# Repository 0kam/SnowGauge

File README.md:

<p align="center">
  <picture>
    <source media="(prefers-color-scheme: dark)" srcset="docs/assets/logo/logo_dark_800.png">
    
  </picture>
</p>

# SnowGauge

山岳・亜高山帯の無人サイトで 2 年間動く、低価格・低消費電力の積雪深ロガーです。
近赤外レーザー測距（TFmini Plus）で雪面までの斜距離を測り、IMU の傾斜で補正して積雪深に換算します。
スマホ（Android Chrome）の Web Bluetooth ページで時刻合わせ・データ回収・設定を行い、電池だけで越冬します。

*SnowGauge is a low-cost, low-power snow-depth logger (NIR laser ToF + XIAO nRF52840 Sense, Zephyr firmware, Web Bluetooth field app). Documentation is in Japanese; the developer docs (`firmware/README.md`, `docs/app/README.md`, `docs/record_format.md`) are in English.*

## はじめての方へ（この順に読む）

| 段階 | 読むもの | 内容 |
|---|---|---|
| 1. 部品を買う | [docs/01_parts.md](docs/01_parts.md)（[CSV](docs/01_parts.csv)） | 購入リスト。基板版・ブレッドボード版・TSD20 版の差分 |
| 2. 組み立てる | [docs/02_assembly.md](docs/02_assembly.md) | ブレッドボード（[配線ガイド](https://0kam.github.io/SnowGauge/breadboard_guide.html)）／基板 v1.2／筐体（検討中） |
| 3. ファームを書く | [docs/03_firmware.md](docs/03_firmware.md) | [Release](https://github.com/0kam/SnowGauge/releases) からダウンロードして USB で書き込み |
| 4. アプリを入れる・使う | [docs/04_app.md](docs/04_app.md) | **アプリ: https://0kam.github.io/SnowGauge/app/** 設置時・巡回時の手順 |
| 5. データを見る | [docs/05_data.md](docs/05_data.md) | CSV の列、品質フラグ、積雪深の再計算 |

文書一覧と「どこを直すとき何を更新するか」は [docs/README.md](docs/README.md) にあります。

## 現地アプリ

スマホの Chrome で https://0kam.github.io/SnowGauge/app/ を開き「ホーム画面に追加」すると、圏外でも起動するアプリになります（[使い方](docs/04_app.md)）。本体なしで画面を試すには [デモ表示](https://0kam.github.io/SnowGauge/app/?demo=1)。

<table align="center"><tr>
  <td valign="top" width="25%"></td>
  <td valign="top" width="25%"></td>
  <td valign="top" width="25%"></td>
  <td valign="top" width="25%"></td>
</tr><tr>
  <td align="center">1. 同期</td><td align="center">2. 観測データ</td><td align="center">3. スケジュール</td><td align="center">4. 設置・基準設定</td>
</tr></table>

## 主な仕様

- 測距: TFmini Plus（近赤外 ToF）。安価な代替として TSD20 版を A/B 比較予定
- MCU: Seeed XIAO nRF52840 Sense（BLE、IMU 内蔵）、Zephyr（nRF Connect SDK v3.4.0）
- 電源: リチウム単 3（Energizer L91）×4。実測スリープ 26 µA（BLE アドバタイズ込み）、測定 1 回 0.037 mAh
- 記録: 40 バイト/回、QSPI フラッシュ上の LittleFS ＋ 内蔵フラッシュへのミラー。8 回/日で 2 年以上
- 通信: BLE（アドバタイズに電池・件数・最終値、SMP でファイル取得と時刻同期、キャリブレーション用 GATT）
- 現地 UI: Web Bluetooth ページ（PWA、オフライン動作、手袋前提の大きなボタン）

## 開発者向け

- 設計仕様書（要件・設計判断・改版履歴）: [SnowGauge_設計仕様書_v0.16.md](SnowGauge_設計仕様書_v0.16.md)
- 基板（KiCad、ガーバー、ピンマップの正）: [pcb/README.md](pcb/README.md)
- ファームウェアのビルド・シェル: [firmware/README.md](firmware/README.md)
- アプリの構成（SMP クライアントの流用方法）: [docs/app/README.md](docs/app/README.md)
- レコード形式・CSV 列定義: [docs/record_format.md](docs/record_format.md)
- 作業引き継ぎ（AI エージェント向け）: [CLAUDE.md](CLAUDE.md)

## 状態（2026-09-04）

基板 v1.2 発注済み（到着 9/10 ごろ）。ブレッドボードでファームウェア（ステップ 1〜4）とアプリの実機確認まで完了。TSD20 版ファームウェア（ステップ 5）は実装・ビルド済みで、ブレッドボード（U2 を F33 に差し替え）での実機確認待ち。次は基板到着後の再測定、筐体。

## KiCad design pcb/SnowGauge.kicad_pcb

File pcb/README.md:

# SnowGauge PCB v1.2 (TFmini Plus / TSD20 common board)

- Board: **64 x 50 mm**, 2-layer, all through-hole. Bottom layer is a GND pour.
- Mounting: 4x M3 (3.2mm) holes at the corners, **57 x 43 mm** center spacing (3.5mm from every edge; hole centers at (3.5, 3.5) / (60.5, 3.5) / (3.5, 46.5) / (60.5, 46.5) from the board's top-left corner).
- Fits the previous prototype enclosure (Takachi BCAP091208G, inner 66 x 96 mm) with the 50mm side across the width.
- Battery terminal J1 exits at the bottom edge; TFmini terminal J2 exits at the right edge.
- Generated programmatically: [generate_board.py](generate_board.py) → `SnowGauge.kicad_pcb` (KiCad 10). DRC: 0 errors, 0 unconnected.
- One board serves both variants: **U2 = NJU7223F50 for TFmini Plus / NJU7223F33 for TSD20** (same pinout).

## Ordering (JLCPCB, ~1 week to Japan)

1. Go to jlcpcb.com → "Add gerber file" → upload `SnowGauge_v1.2_gerbers.zip`
2. Settings: 2 layers, 64x50mm (auto-detected), qty 5 (or 10), 1.6mm, HASL, green — all defaults are fine
3. Shipping: **DHL or OCS Express** (this is what makes it arrive in ~3-4 days; economy mail takes weeks)

## Firmware pin map (matches this board — the single source of truth)

| XIAO pin | Net | Function |
|---|---|---|
| A0 (D0) | ADC_NODE | Battery voltage = reading x2. Divider hangs on VBAT_SW, so **enable SENSOR_EN, then read A0** (v1.2: Q3/R6/D3 deleted — node is 0V during sleep, never above VDD) |
| D4 / D5 | I2C_SDA / I2C_SCL | Spare I2C header J3 (future external IMU) |
| D6 (TX) | UART_TX_MCU | → 1k (R7) → TFmini RX (white) |
| D7 (RX) | UART_RX | ← TFmini TX (green) |
| **D10** | SENSOR_EN | High = sensor rail ON (Q2→Q1). *Changed from D2 in the hand-wiring plan.* |
| 3V3 | 3V3_SYS | Powered from U1 (NJU7223F33) |

## Connectors

- J1 (screw terminal 2P, 5.08mm): battery + / − ("+"/"-" on silk)
- J2 (4 positions at 5.08mm = **two interlocked 2P blocks**): TFmini, top to bottom RED +5V / BLK GND / GRN TX / WHT RX
- J3 (pin header 1x4): SCL / SDA / GND / 3V3 spare I2C
- A1: 2x low-profile 1x7 female headers (2.54mm) — socket for XIAO nRF52840 Sense

## Extra BOM lines (in addition to spec §6)

| Part | Qty | Note |
|---|---|---|
| Screw terminal block 2P, **5.08mm pitch, interlocking** (TB111-2 / MKDS-1,5 type) | 3 | J1 battery; J2 = 2 blocks snapped together (4 contiguous positions) |
| Female pin socket 1x7, 2.54mm | 2 | XIAO socket. Holes are 0.89mm: fine for round machined tails (~0.5mm) and typical stamped tails; avoid 0.64mm square-tail types |
| 10uF radial MLCC, **5mm lead pitch** | 1 | C6. A 2.5mm-pitch part needs its leads splayed |
| Pin header 1x4, 2.54mm | 1 | J3 (optional) |
| M3 screws/standoffs | 4 | mounting holes at corners |

The consolidated BOM for a whole unit (spec §6 parts + these lines, corrected counts, breadboard consumables, TSD20 variant) is [docs/01_parts.md](../docs/01_parts.md) / [docs/01_parts.csv](../docs/01_parts.csv).

## Safety notes silkscreened on the board

- "NO USB WHILE BATTERY CONNECTED!" — disconnect battery before plugging USB into the XIAO
- C4 (OS-CON) polarity marked; D1 cathode marked "K"

## Component orientation (U1, U2, Q1, Q2)

The KiCad TO-220 / TO-251 vertical footprints put the reference designator on the **metal-tab side**, so the part's **marked (printed) face points the other way**. With the board held "SnowGauge v1.2" up / J1 down: U1 and Q1 have the tab towards the top edge (print facing the XIAO), U2 and Q2 are rotated 180 deg (tab towards the board centre, print facing the top edge). Assembly instructions with a figure: [docs/02_assembly.md](../docs/02_assembly.md) B-2 (figure regenerated by `docs/assets/figures/gen_component_orientation.py`).

## v1.2 changes (post-review)

- **Battery divider now fed from VBAT_SW** (the switched rail) instead of VBAT: the ADC node sits at 0V during sleep instead of floating to ~7V through the nRF52840's clamp diode (abs-max violation found in review). Q3, R6 and the D3 GPIO are deleted. Firmware measures battery by enabling SENSOR_EN and reading A0 (x2).
- **USB corridor cleared**: U1 and C1 moved to the top-left, D1 lowered — a USB-C cable now reaches the socketed XIAO for flashing.
- TFmini wire-order legend moved where it stays visible after C4 is mounted.
- Terminals changed to **3x 5.08mm 2P blocks**; the TFmini pair interlocks into one 4P unit on contiguous 5.08mm positions (J2). Standard Akizuki TB111-class parts drop in.

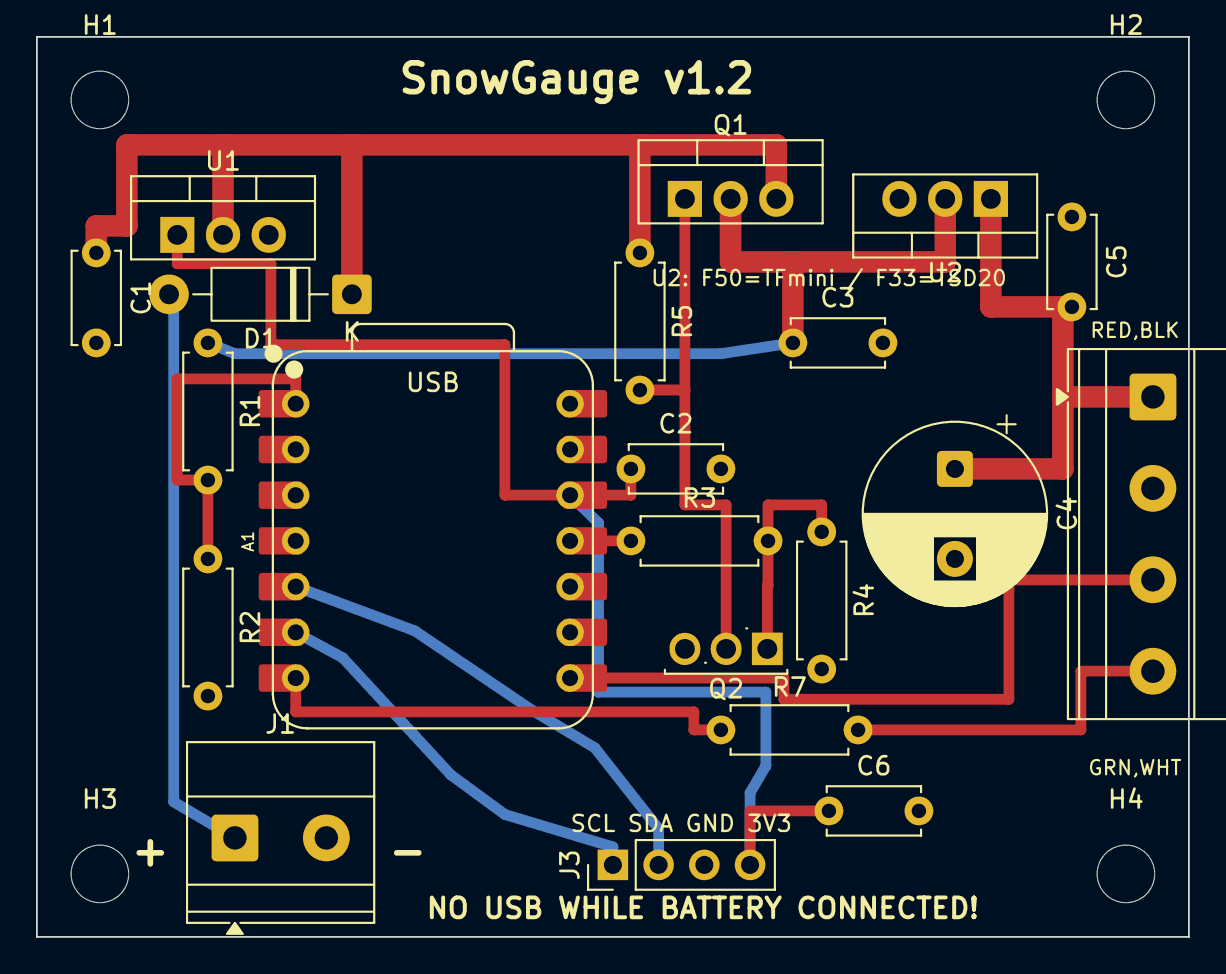
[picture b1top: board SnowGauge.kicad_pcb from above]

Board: 2 copper layers, 64.0 x 50.0 mm, 25 parts (0 on the bottom side), 15 nets.

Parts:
A1: XIAO nRF52840 Sense; XIAO-nRF52840-DIP
C1, C2, C3, C5: 0.1u; C_Disc_D5.0mm_W2.5mm_P5.00mm
C4: OS-CON 470u/16V; CP_Radial_D10.0mm_P5.00mm
C6: 10u; C_Disc_D5.0mm_W2.5mm_P5.00mm
D1: 1N5819; D_DO-41_SOD81_P10.16mm_Horizontal
H1, H2, H3, H4: M3; MountingHole_3.2mm_M3
J1: BATTERY L91x4; TerminalBlock_Phoenix_MKDS-1,5-2-5.08_1x02_P5.08mm_Horizont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
J2: TFmini 2Px2; TerminalBlock_Phoenix_MKDS-1,5-4-5.08_1x04_P5.08mm_Horizont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
J3: I2C SPARE; PinHeader_1x04_P2.54mm_Vertical
Q1: 2SJ334; TO-220-3_Vertical
Q2: 2SK4017; TO-251-3_Vertical
R1, R2: 1M; R_Axial_DIN0207_L6.3mm_D2.5mm_P7.62mm_Horizontal
R3: 10k; R_Axial_DIN0207_L6.3mm_D2.5mm_P7.62mm_Horizontal
R4, R5: 100k; R_Axial_DIN0207_L6.3mm_D2.5mm_P7.62mm_Horizontal
R7: 1k; R_Axial_DIN0207_L6.3mm_D2.5mm_P7.62mm_Horizontal
U1: NJU7223F33; TO-220-3_Vertical
U2: NJU7223F50; TO-220-3_Vertical

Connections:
3V3_SYS: A1.12, C2.1, C6.1, J3.4, U1.1
5V_SENS: C4.1, C5.2, J2.1, U2.1
ADC_NODE: A1.1, R1.2, R2.1
BATP_RAW: D1.2, J1.1
GND: A1.13, C1.2, C2.2, C3.2, C4.2, C5.1, C6.2, J1.2, J2.2, J3.3, Q2.3, R2.2, R4.2, U1.3, U2.3
I2C_SCL: A1.6, J3.1
I2C_SDA: A1.5, J3.2
Q1_GATE: Q1.1, Q2.2, R5.2
Q2_G: Q2.1, R3.2, R4.1
SENSOR_EN: A1.11, R3.1
TFMINI_RX: J2.4, R7.2
UART_RX: A1.8, J2.3
UART_TX_MCU: A1.7, R7.1
VBAT: C1.1, D1.1, Q1.3, R5.1, U1.2
VBAT_SW: C3.1, Q1.2, R1.1, U2.2

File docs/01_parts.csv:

区分,記号,部品,値/型番,数量,購入先リンク,備考
共通,A1,マイコン（IMU・温度・BLE・2MB QSPI内蔵）,Seeed XIAO nRF52840 Sense,1,https://www.switch-science.com/products/8146,~¥3000。展開台数+2〜3台の予備を推奨
共通,-,LiDAR（上位側）,Benewake TFmini Plus,1,https://www.switch-science.com/products/8153,~¥7000〜9000。IP65。ケーブル 赤=+5V/黒=GND/緑=TX/白=RX（現物で要確認）
共通,U1,3.3V LDO（常時ON）,NJU7223F33 (TO-220F 500mA),1,https://akizukidenshi.com/catalog/g/g100432/,¥80。ピン並び VOUT-VIN-GND
共通,U2,5V LDO（測定時のみON）,NJU7223F50 (TO-220F 500mA),1,https://akizukidenshi.com/catalog/g/g100671/,¥50〜80。TSD20版はF33に置き換え
共通,Q1,高側スイッチ P-ch MOSFET,2SJ334 (TO-220),1,https://akizukidenshi.com/catalog/g/g102846/,¥110。ピン並び G-D-S
共通,Q2,ゲート駆動 N-ch MOSFET,2SK4017 (TO-251),1,https://akizukidenshi.com/catalog/g/g107597/,¥30。ピン並び G-D-S。v1.2ではQ2の1個のみ（Q3廃止）
共通,D1,逆接保護ショットキー,1N5819 (40V/1A),1,https://akizukidenshi.com/catalog/g/g117244/,¥100/10本入り。帯（カソード）側がVBAT
共通,"C1,C2,C3,C5",セラミックコンデンサ（パスコン）,0.1µF X7R 50V,4,https://akizukidenshi.com/catalog/g/g113582/,¥100/10個入り
共通,C4,バルクコンデンサ（5Vレール）,OS-CON SEPC 470µF/16V,1,https://akizukidenshi.com/catalog/g/g108292/,~¥200。極性あり（長い足が+）。PCBはφ10mm・5mmピッチ
共通,C6,セラミックコンデンサ（3.3Vレール）,10µF 積層セラミック（極性なし）,1,要選定,PCBは5mmリードピッチ品（2.5mmは足を広げる）
共通,"R1,R2",電池電圧の分圧,1MΩ 1/4W カーボン,2,https://akizukidenshi.com/catalog/g/g125105/,¥120/100本入り。代替: 同じ値なら5kΩ〜1MΩ
共通,R3,Q2ゲート直列,10kΩ 1/4W,1,https://akizukidenshi.com/catalog/g/g125103/,¥120/100本入り。代替: 150Ω〜2.2kΩ（R3=R4=10kはNG）
共通,"R4,R5",Q2プルダウン / Q1 G-Sプルアップ,100kΩ 1/4W,2,要選定（秋月 カーボン抵抗1/4W 100kΩ）,R4・R5の2本（R6廃止）。代替: 10kΩ可
共通,R7,UART TX直列（保護）,1kΩ 1/4W,1,https://akizukidenshi.com/catalog/g/g125102/,¥120/100本入り。代替: 1k〜5kΩ
共通,BT,電池,Energizer L91（単3リチウム）,4,要選定,開放7.2V→終止4.0V。低温特性で最良
共通,-,電池ボックス,単3×4 直列 リード線付き,1,要選定,PCBでは赤→J1「+」、黒→J1「−」
PCB v1.2,-,プリント基板,SnowGauge PCB v1.2 (64x50mm 2層),1,JLCPCB（pcb/SnowGauge_v1.2_gerbers.zip）,最小5枚。02_assembly.md §B参照
PCB v1.2,"J1,J2",ネジ端子台 2P,5.08mmピッチ 連結型 (TB111-2 / MKDS-1.5系),3,要選定（秋月 TB111系）,J1=電池。J2=2個を連結して4極（TFmini）
PCB v1.2,A1ソケット,ピンソケット 1x7 2.54mm 低背,メス 1x7,2,要選定,基板穴0.89mm。0.64mm角ピン品は避ける
PCB v1.2,J3,ピンヘッダ 1x4 2.54mm,オス 1x4,1,要選定,予備I2C。省略可
PCB v1.2,H1-H4,M3ネジ・スペーサ,M3（穴φ3.2）,4,要選定,四隅 穴中心間57x43mm
ブレッドボード,-,ブレッドボード,830穴,1,要選定,breadboard_guide.htmlはこのサイズ前提
ブレッドボード,-,ジャンパワイヤ,単線ジャンパ各色 + オス-オス数本,1セット,要選定,電源系は短く太いもの
ブレッドボード,-,電源,安定化電源 6.0V 電流制限1A以上 または 電池ボックス+L91x4,1,要選定,スリープ電流測定は電池と直列のµA電流計
ブレッドボード,-,TFmini接続補助,ピンヘッダ付きジャンパ または 圧着ピン,適量,要選定,TFminiの線は細く抜けやすい
ブレッドボード,-,テスター,DC電圧 0.01V単位,1,要選定,各STEPの確認に必須
TSD20版,-,LiDAR（廉価側）,PONO TSD20,1,https://akizukidenshi.com/catalog/g/g131304/,¥2580。TFmini Plusの代わり。FW未作成
TSD20版,U2,3.3V LDO（測定時のみON）,NJU7223F33（2個目）,1,https://akizukidenshi.com/catalog/g/g100432/,NJU7223F50の代わり
